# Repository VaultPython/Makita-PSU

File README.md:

# Makita-PSU
A easy to use 2-Channel PSU, based on a makita 18 Volt Battery.

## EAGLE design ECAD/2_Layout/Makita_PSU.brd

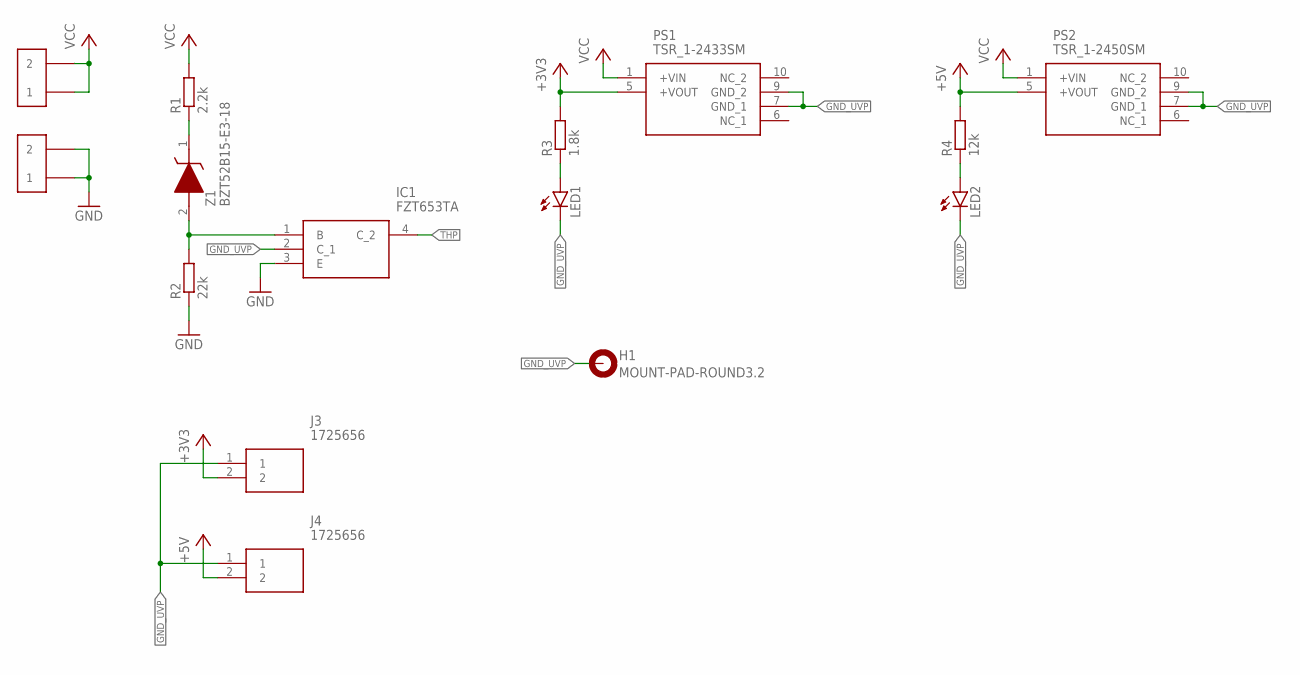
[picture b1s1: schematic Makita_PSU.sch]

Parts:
H1: MOUNT-PAD-ROUND3.2; 3,2-PAD
IC1: FZT653TA; SOT230P700X180-4N
J1, J2: VOGT_3825Z.68
J3, J4: 1725656
LED1, LED2: LEDCHIPLED_0805; CHIPLED_0805
PS1: TSR_1-2433SM; TSR124120SM
PS2: TSR_1-2450SM; TSR124120SM
R1: 2.2k; R0805
R2: 22k; R0805
R3: 1.8k; R0805
R4: 12k; R0805
Z1: BZT52B15-E3-18; SOD3716X135N

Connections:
+3V3: J3.2, PS1.5 (+VOUT), R3.2
+5V: J4.2, PS2.5 (+VOUT), R4.2
GND: IC1.3 (E), J2.P$1 (1), J2.P$2 (2), R2.1
GND_UVP: H1.B3,2, IC1.2 (C_1), J3.1, J4.1, LED1.C, LED2.C, PS1.7 (GND_1), PS1.9 (GND_2), PS2.7 (GND_1), PS2.9 (GND_2)
unnamed: IC1.1 (B), R2.2, Z1.2 (A)
unnamed: R1.1, Z1.1 (K)
unnamed: LED1.A, R3.1
unnamed: LED2.A, R4.1
THP: IC1.4 (C_2)
VCC: J1.P$1 (1), J1.P$2 (2), PS1.1 (+VIN), PS2.1 (+VIN), R1.2

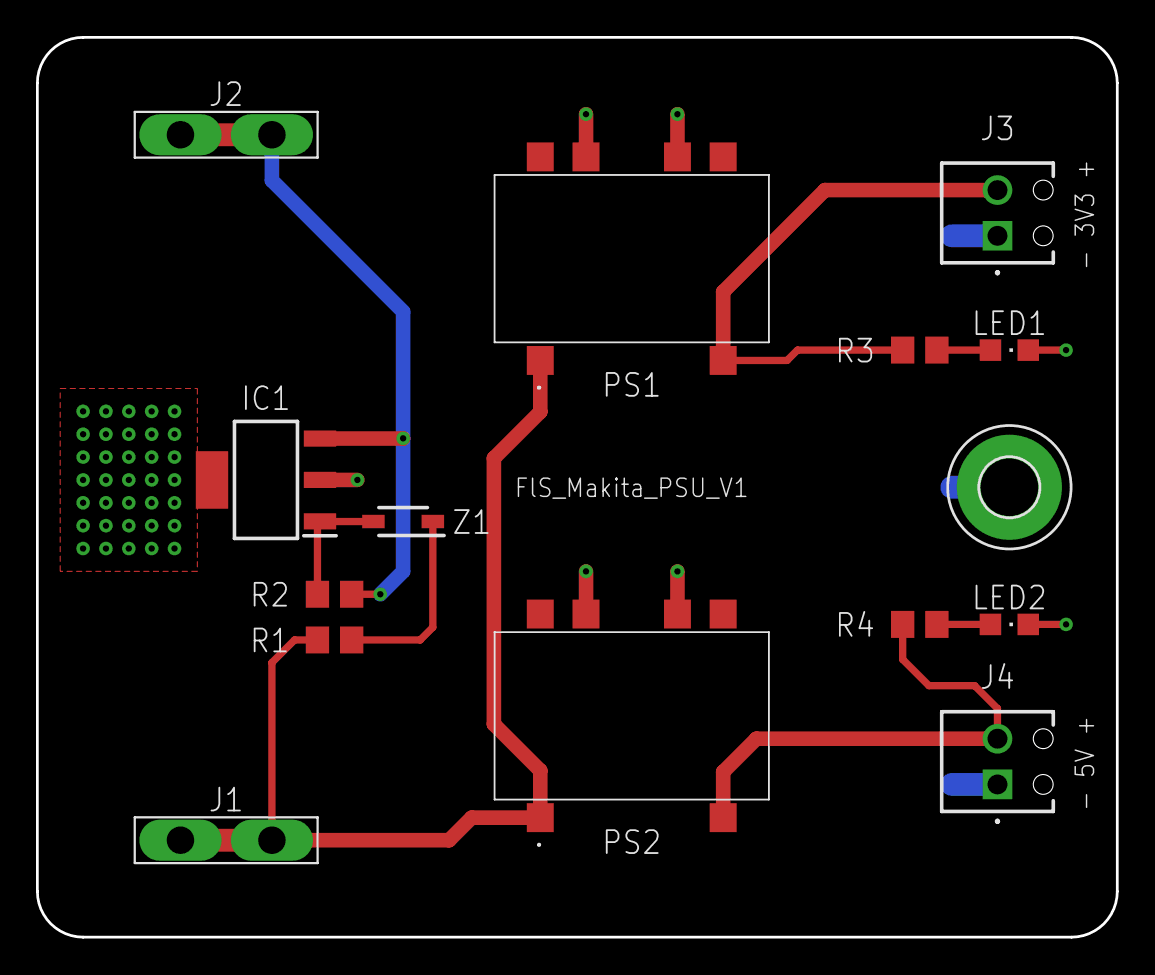
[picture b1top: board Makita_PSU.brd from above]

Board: 2 copper layers, 60.0 x 50.0 mm, 15 parts (0 on the bottom side), 9 nets.

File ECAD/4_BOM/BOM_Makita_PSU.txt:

Stückliste exportiert aus C:/Users/Flori/OneDrive/Dokumente/EAGLE/projects/Makita_PSU/Makita_PSU.sch am 25.10.2022 12:49

Qty Value              Device             Package           Parts      Description                                                                                                                                                                                                                                                                                                                                                                                                                                                      
2                      LEDCHIPLED_0805    CHIPLED_0805      LED1, LED2 LED                                                                                                                                                                                                                                                                                                                                                                                                                                                              
1   1.8k               R-EU_R0805         R0805             R3         RESISTOR, European symbol                                                                                                                                                                                                                                                                                                                                                                                                                                        
1   12k                R-EU_R0805         R0805             R4         RESISTOR, European symbol                                                                                                                                                                                                                                                                                                                                                                                                                                        
2   1725656            1725656            1725656           J3, J4     PCB terminal block, nominal current: 6 A, rated voltage (III/2): 160 V, nominal cross section: 0.5 mm?, Number of potentials: 2, Number of rows: 1, Number of positions per row: 2, product range: MPT 0,5, pitch: 2.54 mm, connection method: Screw connection with tension sleeve, mounting: Wave soldering, conductor/PCB connection direction: 0 ?, color: green, Pin layout: Linear pinning, Solder pin [P]: 3.5 mm, type of packaging: packed in cardboard 
1   2.2k               R-EU_R0805         R0805             R1         RESISTOR, European symbol                                                                                                                                                                                                                                                                                                                                                                                                                                        
1   22k                R-EU_R0805         R0805             R2         RESISTOR, European symbol                                                                                                                                                                                                                                                                                                                                                                                                                                        
1   BZT52B15-E3-18     BZT52B15-E3-18     SOD3716X135N      Z1         Zener Diodes 15 Volt 0.5W 2%                                                                                                                                                                                                                                                                                                                                                                                                                                     
1   FZT653TA           FZT653TA           SOT230P700X180-4N IC1        Bipolar Transistors - BJT NPN Medium Power                                                                                                                                                                                                                                                                                                                                                                                                                       
1   MOUNT-PAD-ROUND3.2 MOUNT-PAD-ROUND3.2 3,2-PAD           H1         MOUNTING PAD, round                                                                                                                                                                                                                                                                                                                                                                                                                                              
1   TSR_1-2433SM       TSR_1-2433SM       TSR124120SM       PS1        1 Amp POL switching regulator, 3.0 to -36 VDC input, pos.-pos. circuit, SMD package                                                                                                                                                                                                                                                                                                                                                                              
1   TSR_1-2450SM       TSR_1-2450SM       TSR124120SM       PS2        1 Amp POL switching regulator, 3.0 to -36 VDC input, pos.-pos. circuit, SMD package                                                                                                                                                                                                                                                                                                                                                                              
2   VOGT_3825Z.68      VOGT_3825Z.68      VOGT_3825Z.68     J1, J2

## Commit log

2022-10-25 Added Folder for 3d ECAD Files with content
